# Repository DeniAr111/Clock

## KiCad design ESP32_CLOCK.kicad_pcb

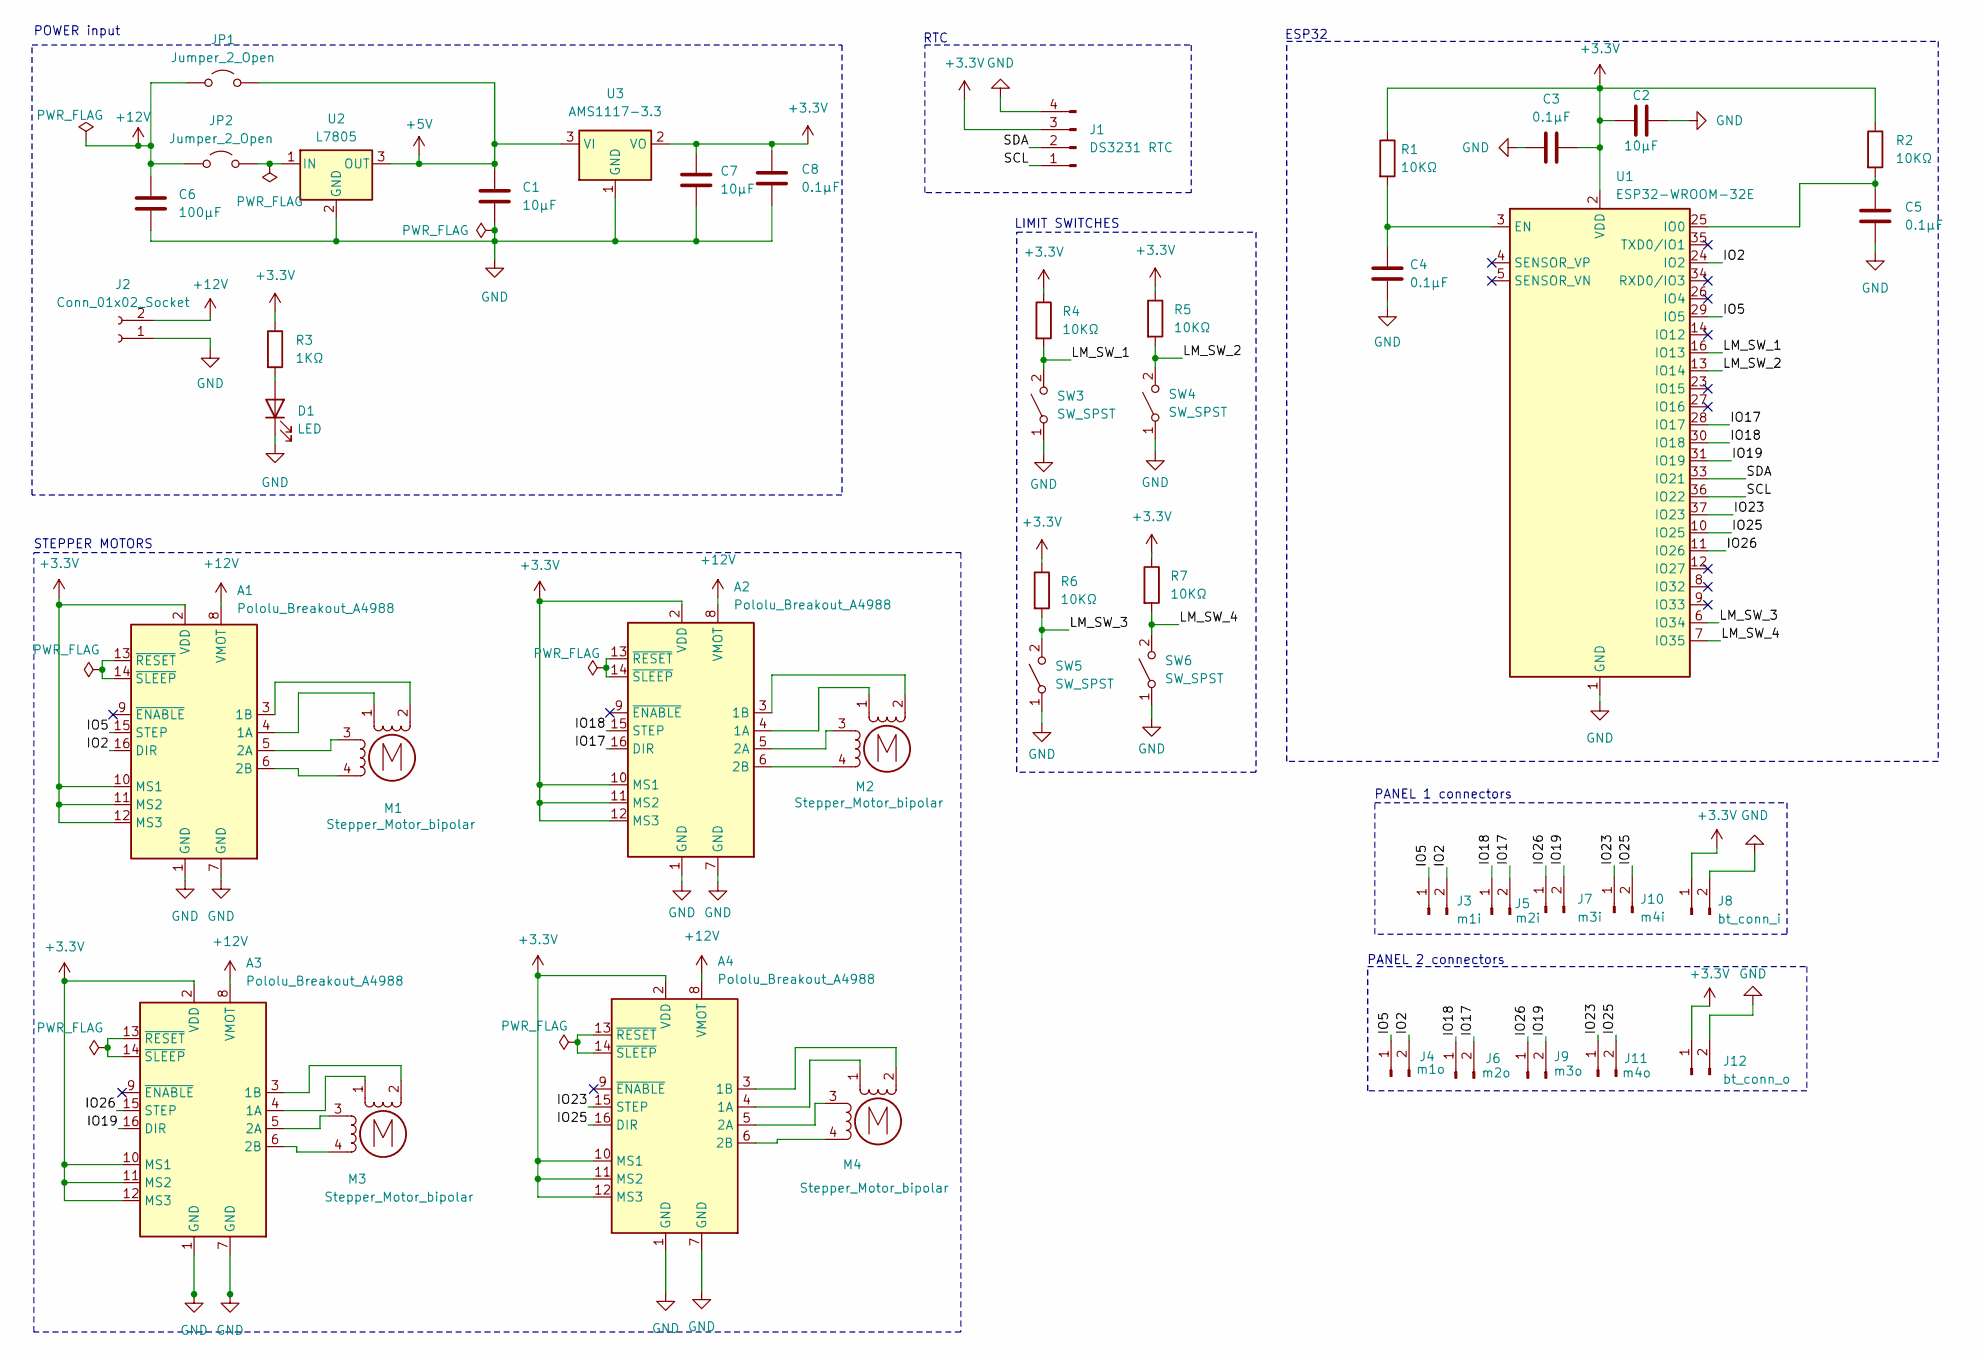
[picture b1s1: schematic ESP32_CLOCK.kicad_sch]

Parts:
A1, A2, A3, A4: Pololu_Breakout_A4988; Pololu_Breakout-16_15.2x20.3mm
C1, C2, C7: 10μF; C_0805_2012Metric
C3, C4, C5, C8: 0.1μF; C_0805_2012Metric
C6: 100μF; C_0805_2012Metric
D1: LED; D_0805_2012Metric
J1: DS3231 RTC; SOIC-16W_7.5x10.3mm_P1.27mm
J2: Conn_01x02_Socket; JWT_A3963_1x02_P3.96mm_Vertical
J3: m1i; PinHeader_1x02_P2.54mm_Vertical
J4: m1o; PinHeader_1x02_P2.54mm_Vertical
J5: m2i; PinHeader_1x02_P2.54mm_Vertical
J6: m2o; PinHeader_1x02_P2.54mm_Vertical
J7: m3i; PinHeader_1x02_P2.54mm_Vertical
J8: bt_conn_i; PinHeader_1x02_P2.54mm_Vertical
J9: m3o; PinHeader_1x02_P2.54mm_Vertical
J10: m4i; PinHeader_1x02_P2.54mm_Vertical
J11: m4o; PinHeader_1x02_P2.54mm_Vertical
J12: bt_conn_o; PinHeader_1x02_P2.54mm_Vertical
JP1, JP2: Jumper_2_Open; PinHeader_1x02_P2.54mm_Vertical
M1, M2, M3, M4: Stepper_Motor_bipolar; Molex_KK-254_AE-6410-04A_1x04_P2.54mm_Vertical
R1, R2, R4, R5, R6, R7: 10KΩ; R_0805_2012Metric
R3: 1KΩ; R_0805_2012Metric
SW3, SW4, SW5, SW6: SW_SPST; PinHeader_1x03_P2.54mm_Vertical
U1: ESP32-WROOM-32E; ESP32-WROOM-32D
U2: L7805; TO-220-3_Vertical
U3: AMS1117-3.3; TO-252-2

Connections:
+3.3V: A1.2 (VDD), A1.10 (MS1), A1.11 (MS2), A1.12 (MS3), A2.2 (VDD), A2.10 (MS1), A2.11 (MS2), A2.12 (MS3), A3.2 (VDD), A3.10 (MS1), A3.11 (MS2), A3.12 (MS3), A4.2 (VDD), A4.10 (MS1), A4.11 (MS2), A4.12 (MS3), C2.2, C3.2, C7.1, C8.1, J1.3, J8.1, J12.1, R1.1, R2.1, R3.1, R4.1, R5.1, R6.1, R7.1, U1.2 (VDD), U3.2 (VO)
+5V: C1.1, JP1.2 (B), U2.3 (OUT), U3.3 (VI)
+12V: A1.8 (VMOT), A2.8 (VMOT), A3.8 (VMOT), A4.8 (VMOT), C6.1, J2.2, JP1.1 (A), JP2.1 (A)
/IO2: A1.16 (DIR), J3.2, J4.2, U1.24 (IO2)
/IO5: A1.15 (STEP), J3.1, J4.1, U1.29 (IO5)
/IO17: A2.16 (DIR), J5.2, J6.2, U1.28 (IO17)
/IO18: A2.15 (STEP), J5.1, J6.1, U1.30 (IO18)
/IO19: A3.16 (DIR), J7.2, J9.2, U1.31 (IO19)
/IO23: A4.15 (STEP), J10.1, J11.1, U1.37 (IO23)
/IO25: A4.16 (DIR), J10.2, J11.2, U1.10 (IO25)
/IO26: A3.15 (STEP), J7.1, J9.1, U1.11 (IO26)
/LM_SW_1: R4.2, SW3.2 (B), U1.16 (IO13)
/LM_SW_2: R5.2, SW4.2 (B), U1.13 (IO14)
/LM_SW_3: R6.2, SW5.2 (B), U1.6 (IO34)
/LM_SW_4: R7.2, SW6.2 (B), U1.7 (IO35)
/SCL: J1.1, U1.36 (IO22)
/SDA: J1.2, U1.33 (IO21)
GND: A1.1 (GND), A1.7 (GND), A2.1 (GND), A2.7 (GND), A3.1 (GND), A3.7 (GND), A4.1 (GND), A4.7 (GND), C1.2, C2.1, C3.1, C4.2, C5.2, C6.2, C7.2, C8.2, D1.1 (K), J1.4, J2.1, J8.2, J12.2, SW3.1 (A), SW4.1 (A), SW5.1 (A), SW6.1 (A), U1.1 (GND), U1.15 (GND), U1.38 (GND), U1.39 (GND), U2.2 (GND), U3.1 (GND)
unnamed: A1.4 (1A), M1.1
unnamed: A1.3 (1B), M1.2 (-)
unnamed: A1.5 (2A), M1.3
unnamed: A1.6 (2B), M1.4
unnamed: A1.13 (~RESET), A1.14 (~SLEEP)
unnamed: A2.4 (1A), M2.1
unnamed: A2.3 (1B), M2.2 (-)
unnamed: A2.5 (2A), M2.3
unnamed: A2.6 (2B), M2.4
unnamed: A2.13 (~RESET), A2.14 (~SLEEP)
unnamed: A3.4 (1A), M3.1
unnamed: A3.3 (1B), M3.2 (-)
unnamed: A3.5 (2A), M3.3
unnamed: A3.6 (2B), M3.4
unnamed: A3.13 (~RESET), A3.14 (~SLEEP)
unnamed: A4.4 (1A), M4.1
unnamed: A4.3 (1B), M4.2 (-)
unnamed: A4.5 (2A), M4.3
unnamed: A4.6 (2B), M4.4
unnamed: A4.13 (~RESET), A4.14 (~SLEEP)
unnamed: D1.2 (A), R3.2
unnamed: JP2.2 (B), U2.1 (IN)
unnamed: C4.1, R1.2, U1.3 (EN)
unnamed: C5.1, R2.2, U1.25 (IO0)

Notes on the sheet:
RTC
ESP32
STEPPER MOTORS
PANEL 2 connectors
PANEL 1 connectors
LIMIT SWITCHES
POWER input

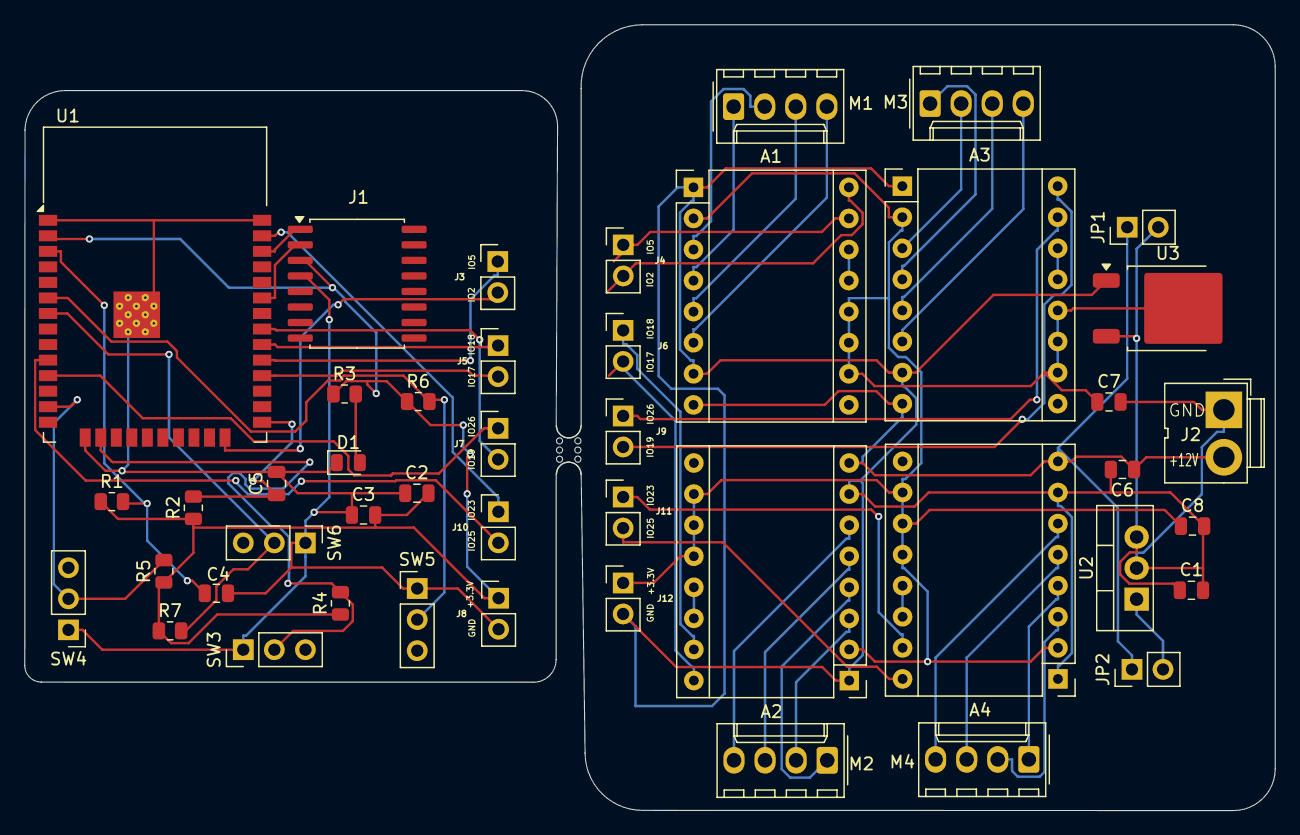
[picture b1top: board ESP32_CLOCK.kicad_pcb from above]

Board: 2 copper layers, 102.2 x 64.2 mm, 46 parts (0 on the bottom side), 42 nets.

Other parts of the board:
mouse-bite-2mm-slot: VAL**; mouse-bite-2mm-slot

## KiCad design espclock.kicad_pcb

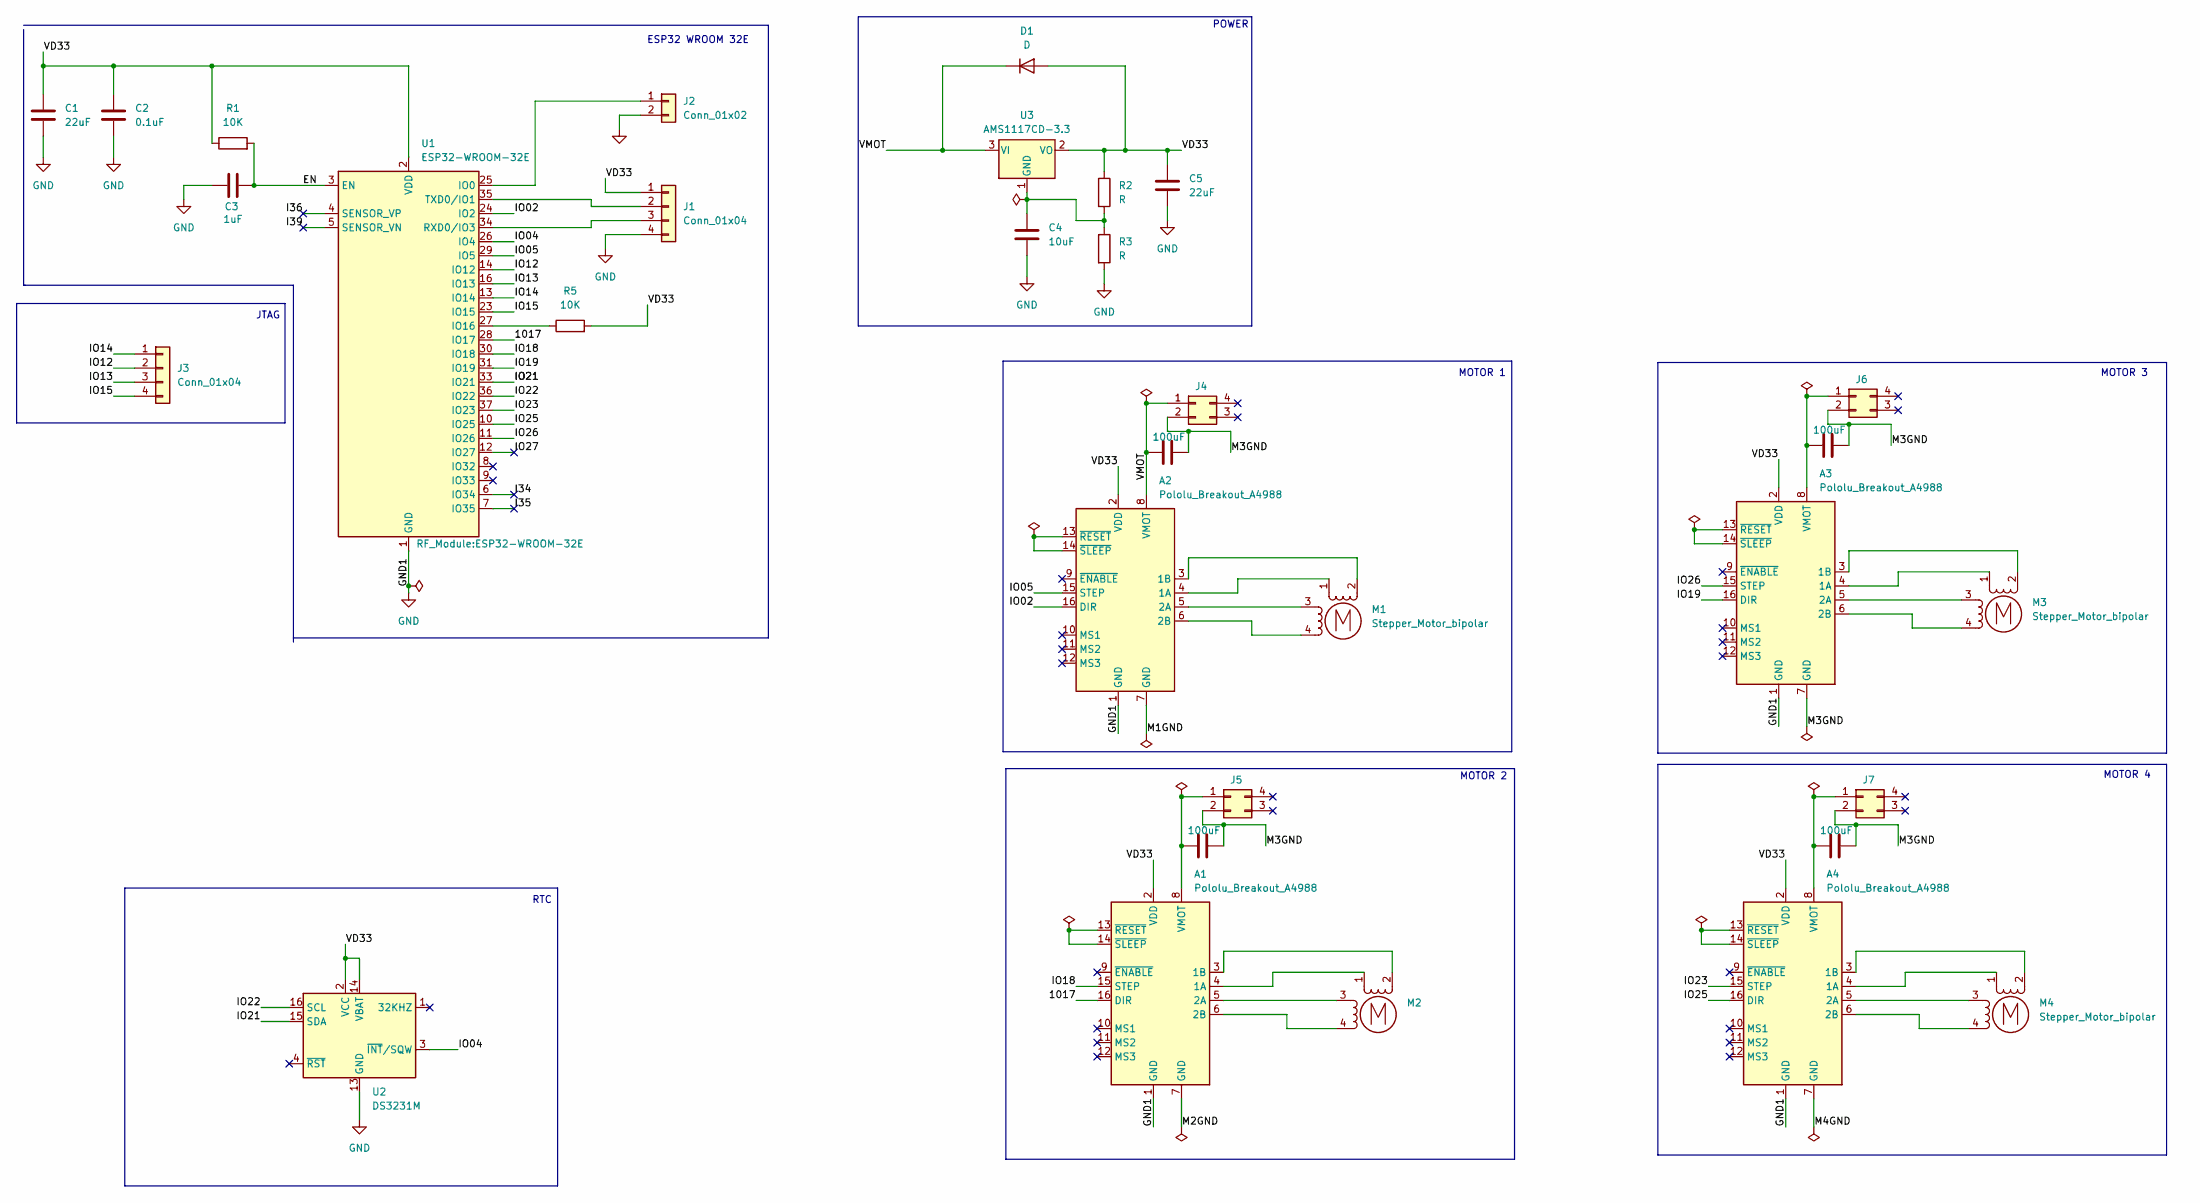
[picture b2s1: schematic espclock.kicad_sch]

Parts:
A1, A2, A3, A4: Pololu_Breakout_A4988; Pololu_Breakout-16_15.2x20.3mm
C1, C5: 22uF; C_0805_2012Metric
C2: 0.1uF; C_0805_2012Metric
C3: 1uF; C_0805_2012Metric
C4: 10uF; C_0805_2012Metric
C7, C8, C9, C10: 100uF; C_0805_2012Metric
D1: D; D_0805_2012Metric
J1, J3: Conn_01x04; PinHeader_1x04_P2.54mm_Horizontal
J2: Conn_01x02; PinHeader_1x02_P2.54mm_Horizontal
J4, J5, J6, J7: Conn_02x02_Counter_Clockwise; PinHeader_2x02_P2.54mm_Horizontal
M1, M2, M3, M4: Stepper_Motor_bipolar; Molex_KK-254_AE-6410-04A_1x04_P2.54mm_Vertical
R1, R5: 10K; R_0805_2012Metric
R2, R3: R; R_0805_2012Metric
U1: ESP32-WROOM-32E
U2: DS3231M; SOIC-16W_7.5x10.3mm_P1.27mm
U3: AMS1117CD-3.3; SOT-223

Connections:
/1017: A1.16 (DIR), U1.28 (IO17)
/EN: C3.2, R1.2, U1.3 (EN)
/I34: U1.6 (IO34)
/I35: U1.7 (IO35)
/I36: U1.4 (SENSOR_VP)
/I39: U1.5 (SENSOR_VN)
/IO02: A2.16 (DIR), U1.24 (IO2)
/IO04: U1.26 (IO4), U2.3 (~INT/SQW)
/IO05: A2.15 (STEP), U1.29 (IO5)
/IO12: J3.2, U1.14 (IO12)
/IO13: J3.3, U1.16 (IO13)
/IO14: J3.1, U1.13 (IO14)
/IO15: J3.4, U1.23 (IO15)
/IO18: A1.15 (STEP), U1.30 (IO18)
/IO19: A3.16 (DIR), U1.31 (IO19)
/IO21: U1.33 (IO21), U2.15 (SDA)
/IO22: U1.36 (IO22), U2.16 (SCL)
/IO23: A4.15 (STEP), U1.37 (IO23)
/IO25: A4.16 (DIR), U1.10 (IO25)
/IO26: A3.15 (STEP), U1.11 (IO26)
/IO27: U1.12 (IO27)
/M1GND: A2.7 (GND)
/M2GND: A1.7 (GND)
/M3GND: A3.7 (GND), C7.1, C8.1, C9.1, C10.1, J4.2, J5.2, J6.2, J7.2
/M4GND: A4.7 (GND)
/VD33: A1.2 (VDD), A2.2 (VDD), A3.2 (VDD), A4.2 (VDD), C1.1, C2.1, C5.1, D1.2 (A), J1.1, R1.1, R2.1, R5.2, U1.2 (VDD), U2.2 (VCC), U2.14 (VBAT), U3.2 (VO)
/VMOT: A2.8 (VMOT), C8.2, D1.1 (K), J4.1, U3.3 (VI)
GND: A1.1 (GND), A2.1 (GND), A3.1 (GND), A4.1 (GND), C1.2, C2.2, C3.1, C4.2, C5.2, J1.4, J2.2, R3.2, U1.1 (GND), U1.15 (GND), U1.38 (GND), U1.39 (GND), U2.5 (GND), U2.6 (GND), U2.7 (GND), U2.8 (GND), U2.9 (GND), U2.10 (GND), U2.11 (GND), U2.12 (GND), U2.13 (GND)
unnamed: A1.4 (1A), M2.1
unnamed: A1.3 (1B), M2.2 (-)
unnamed: A1.5 (2A), M2.3
unnamed: A1.6 (2B), M2.4
unnamed: A1.8 (VMOT), C9.2, J5.1
unnamed: A1.13 (~RESET), A1.14 (~SLEEP)
unnamed: A2.4 (1A), M1.1
unnamed: A2.3 (1B), M1.2 (-)
unnamed: A2.5 (2A), M1.3
unnamed: A2.6 (2B), M1.4
unnamed: A2.13 (~RESET), A2.14 (~SLEEP)
unnamed: A3.4 (1A), M3.1
unnamed: A3.3 (1B), M3.2 (-)
unnamed: A3.5 (2A), M3.3
unnamed: A3.6 (2B), M3.4
unnamed: A3.8 (VMOT), C7.2, J6.1
unnamed: A3.13 (~RESET), A3.14 (~SLEEP)
unnamed: A4.4 (1A), M4.1
unnamed: A4.3 (1B), M4.2 (-)
unnamed: A4.5 (2A), M4.3
unnamed: A4.6 (2B), M4.4
unnamed: A4.8 (VMOT), C10.2, J7.1
unnamed: A4.13 (~RESET), A4.14 (~SLEEP)
unnamed: J1.2, U1.35 (TXD0/IO1)
unnamed: J1.3, U1.34 (RXD0/IO3)
unnamed: J2.1, U1.25 (IO0)
unnamed: R5.1, U1.27 (IO16)
unnamed: C4.1, R2.2, R3.1, U3.1 (GND)

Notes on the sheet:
MOTOR 1
MOTOR 2
MOTOR 4
ESP32 WROOM 32E
POWER
RTC
JTAG
MOTOR 3

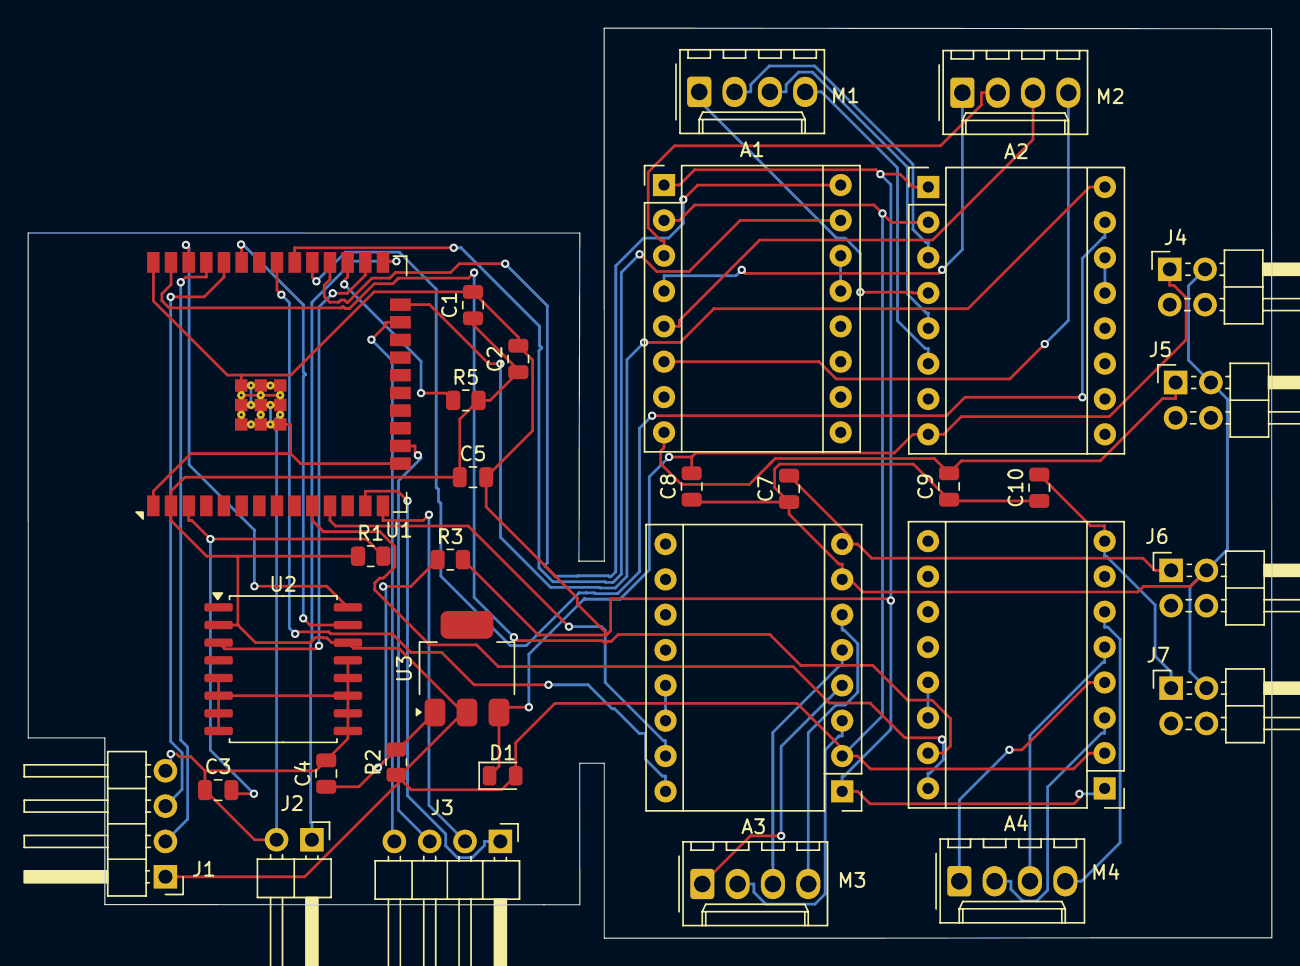
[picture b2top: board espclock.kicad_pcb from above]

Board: 2 copper layers, 89.4 x 65.4 mm, 32 parts (0 on the bottom side), 48 nets.

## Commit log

2025-06-24 Designed PCB layout
